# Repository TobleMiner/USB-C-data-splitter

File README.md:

USB Type C data splitter
========================

This board is a simple splitter that divides a USB Type C connection by data and power domain into two ports.

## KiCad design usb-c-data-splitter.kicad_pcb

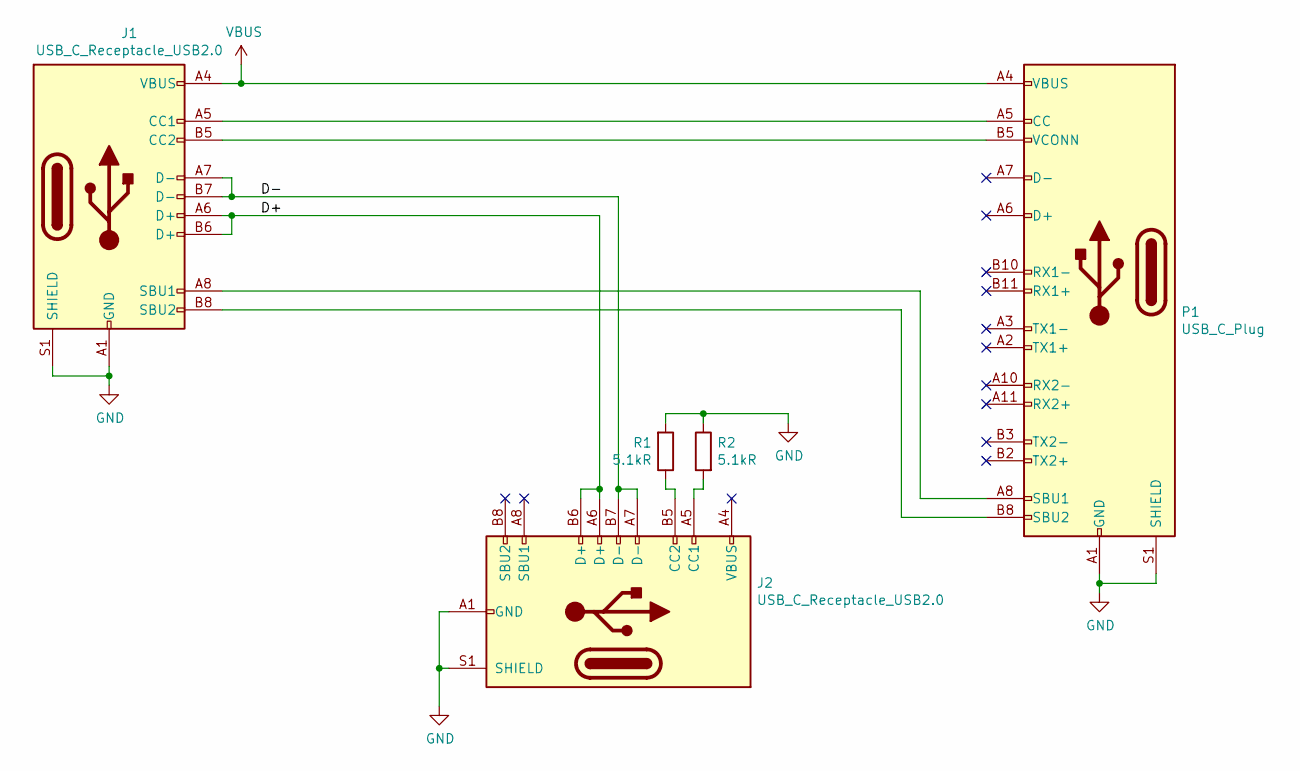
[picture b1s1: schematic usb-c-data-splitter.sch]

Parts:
J1, J2: USB_C_Receptacle_USB2.0; USB_C_Receptacle_Palconn_UTC16-G
P1: USB_C_Plug; U261-24XN-4BS60
R1, R2: 5.1kR; R_0402_1005Metric

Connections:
/D+: J1.A6 (D+), J1.B6 (D+), J2.A6 (D+), J2.B6 (D+)
/D-: J1.A7 (D-), J1.B7 (D-), J2.A7 (D-), J2.B7 (D-)
GND: J1.A1 (GND), J1.A12 (GND), J1.B1 (GND), J1.B12 (GND), J1.S1 (SHIELD), J2.A1 (GND), J2.A12 (GND), J2.B1 (GND), J2.B12 (GND), J2.S1 (SHIELD), P1.A1 (GND), P1.A12 (GND), P1.B1 (GND), P1.B12 (GND), P1.S1 (SHIELD), R1.2, R2.1
unnamed: J1.A5 (CC1), P1.A5 (CC)
unnamed: J1.A8 (SBU1), P1.A8 (SBU1)
unnamed: J1.B5 (CC2), P1.B5 (VCONN)
unnamed: J1.B8 (SBU2), P1.B8 (SBU2)
unnamed: J2.A4 (VBUS), J2.A9 (VBUS), J2.B4 (VBUS), J2.B9 (VBUS)
unnamed: J2.A5 (CC1), R2.2
unnamed: J2.B5 (CC2), R1.1
VBUS: J1.A4 (VBUS), J1.A9 (VBUS), J1.B4 (VBUS), J1.B9 (VBUS), P1.A4 (VBUS), P1.A9 (VBUS), P1.B4 (VBUS), P1.B9 (VBUS)

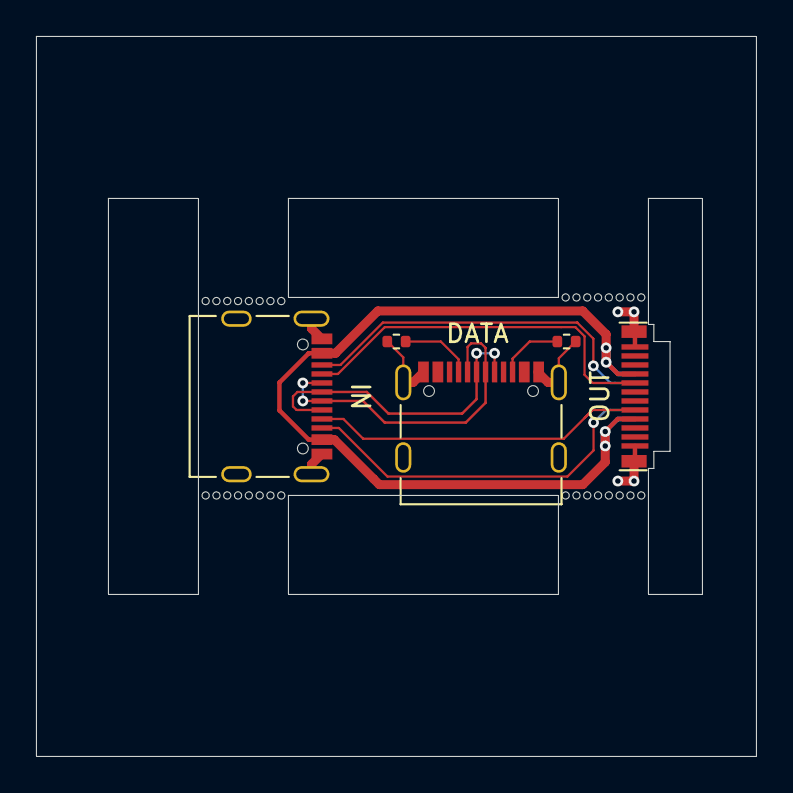
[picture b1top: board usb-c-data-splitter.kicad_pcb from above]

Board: 2 copper layers, 40.0 x 40.0 mm, 5 parts (0 on the bottom side), 11 nets.

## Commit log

2020-10-08 Add README
2020-10-08 Remove duplicate fab.zip
